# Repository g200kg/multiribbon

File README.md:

# multiribbon

## 開発中

現在開発中の謎楽器です。

複数のリボンコントローラーを並列に並べたフレットレスなギターのような演奏を想定しています。

MCU として XIAO RA4M1 を使用

## Demo

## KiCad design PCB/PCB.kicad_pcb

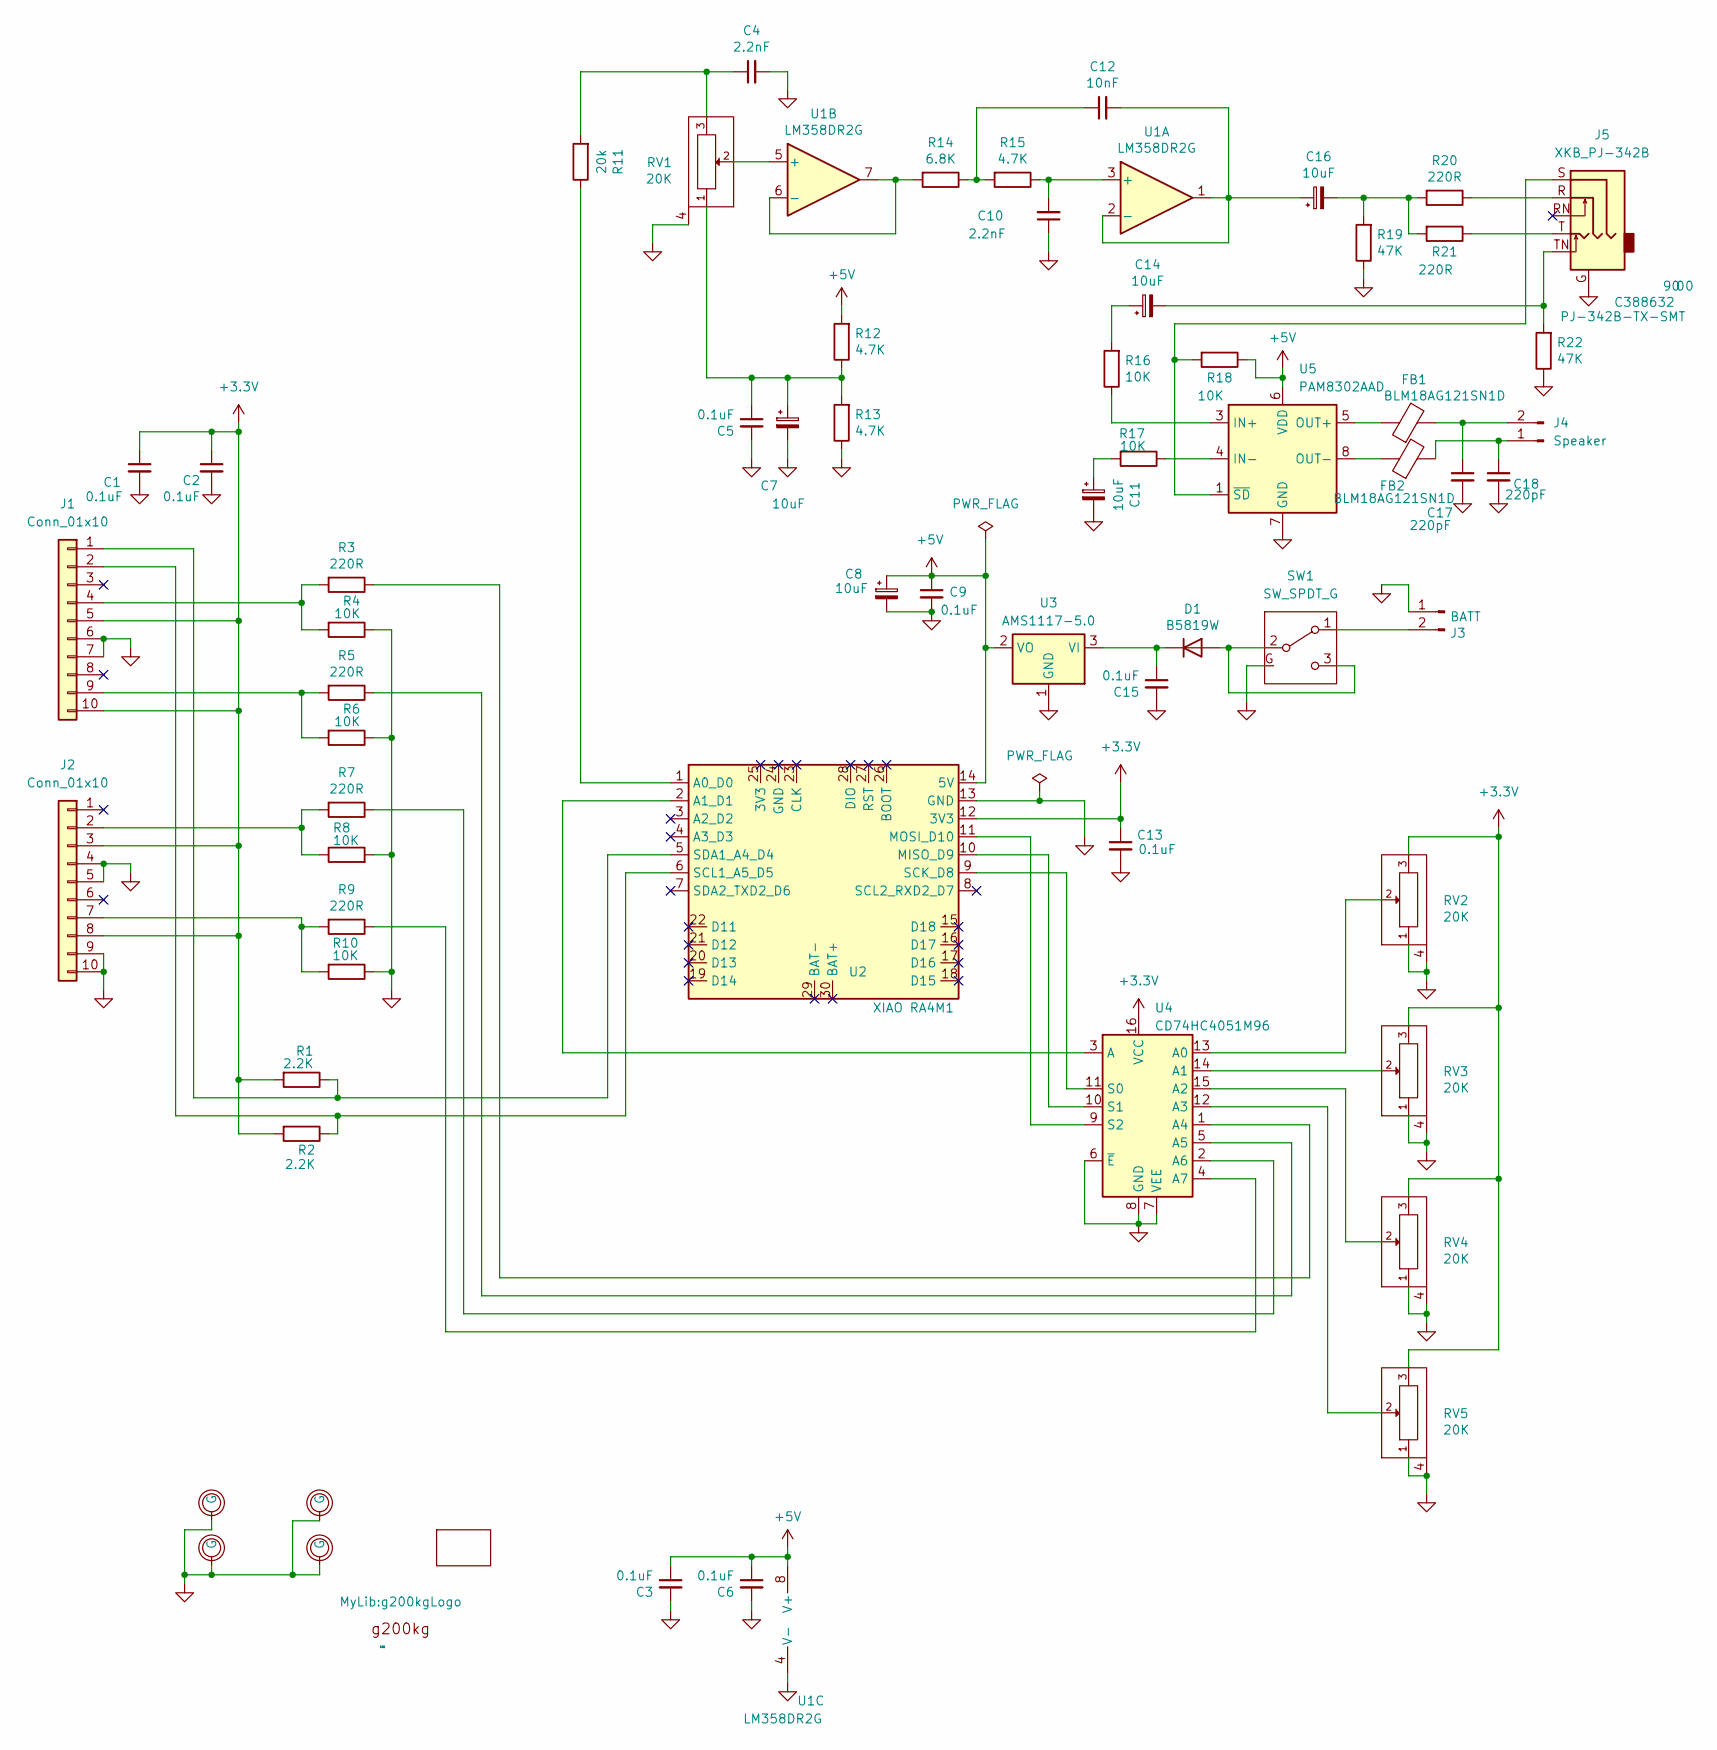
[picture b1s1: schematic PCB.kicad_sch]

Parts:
C1, C2, C3, C5, C6, C9, C13, C15: 0.1uF; C_0603_1608Metric
C4, C10: 2.2nF; C_0603_1608Metric
C7, C8, C11, C14, C16: 10uF; CP_EIA-3216-18_Kemet-A
C12: 10nF; C_0603_1608Metric
C17, C18: 220pF; C_0603_1608Metric
D1: B5819W; D_SOD-123
FB1, FB2: BLM18AG121SN1D; L_0603_1608Metric; LCSC GZ1608D601TF
H1, H2, H3, H4: Hole; MountingHole_3.2mm_M3_DIN965_Pad
J1, J2: Conn_01x10; PinSocket_1x10_P2.54mm_Horizontal
J3: BATT; SolderWire-0.25sqmm_1x02_P4.2mm_D0.65mm_OD1.7mm_Relief
J4: Speaker; JST_PH_S2B-PH-K_1x02_P2.00mm_Horizontal
J5: XKB_PJ-342B; Jack_3.5mm_XKB_PJ342B-TX; LCSC C388632
LG1: LOGO; g200kgLogo
M1: ModuleNC; 006P
R1, R2: 2.2K; R_0603_1608Metric
R3, R5, R7, R9, R20, R21: 220R; R_0603_1608Metric
R4, R6, R8, R10, R16, R17, R18: 10K; R_0603_1608Metric
R11: 20k; R_0603_1608Metric
R12, R13, R15: 4.7K; R_0603_1608Metric
R14: 6.8K; R_0603_1608Metric
R19, R22: 47K; R_0603_1608Metric
RV1, RV2, RV3, RV4, RV5: 20K; Potentiometer_Alps_RK09K_Single_Vertical
SW1: SW_SPDT_G; Sw_Rocker_4MS1R202M6QES
U1: LM358DR2G; SOIC-8_3.9x4.9mm_P1.27mm; LCSC C7950
U2: XIAO RA4M1; XIAO-RA4M1-SMD
U3: AMS1117-5.0; SOT-223-3_TabPin2
U4: CD74HC4051M96; SO-16_3.9x9.9mm_P1.27mm
U5: PAM8302AAD; SOIC-8_3.9x4.9mm_P1.27mm

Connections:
+3.3V: C1.1, C2.1, C13.1, J1.5, J1.10, J2.3, J2.8, R1.2, R2.2, RV2.3, RV3.3, RV4.3, RV5.3, U2.12 (3V3), U4.16 (VCC)
+5V: C3.1, C6.1, C8.1, C9.1, R12.2, R18.1, U1.8 (V+), U2.14 (5V), U3.2 (VO), U5.6 (VDD)
GNDD: C1.2, C2.2, C3.2, C4.2, C5.2, C6.2, C7.2, C8.2, C9.2, C10.1, C11.2, C13.2, C15.2, C17.2, C18.2, H1.1 (G), H2.1 (G), H3.1 (G), H4.1 (G), J1.6, J1.7, J2.4, J2.5, J2.9, J2.10, J3.1, J5.G, R4.1, R6.1, R8.2, R10.1, R13.1, R19.1, R22.1, RV1.4 (G), RV2.1, RV2.4 (G), RV3.1, RV3.4 (G), RV4.1, RV4.4 (G), RV5.1, RV5.4 (G), SW1.G, U1.4 (V-), U2.13 (GND), U3.1 (GND), U4.6 (~E), U4.7 (VEE), U4.8 (GND), U5.7 (GND)
unnamed: C4.1, R11.2, RV1.3
unnamed: C5.1, C7.1, R12.1, R13.2, RV1.1
unnamed: C11.1, R17.2
unnamed: C12.1, R14.1, R15.2
unnamed: C14.1, R16.2
unnamed: C14.2, J5.TN, R22.2
unnamed: C16.2, R19.2, R20.2, R21.2
unnamed: D1.2 (A), SW1.2 (B), SW1.3 (C)
unnamed: C15.1, D1.1 (K), U3.3 (VI)
unnamed: J1.1, R1.1, U2.5 (SDA1_A4_D4)
unnamed: J1.2, R2.1, U2.6 (SCL1_A5_D5)
unnamed: J1.4, R3.2, R4.2
unnamed: J1.9, R5.2, R6.2
unnamed: J2.2, R7.2, R8.1
unnamed: J2.7, R9.2, R10.2
unnamed: J3.2, SW1.1 (A)
unnamed: C18.1, FB2.2, J4.1
unnamed: C17.1, FB1.2, J4.2
unnamed: J5.R, R20.1
unnamed: J5.T, R21.1
unnamed: C10.2, R15.1, U1.3 (+)
unnamed: C12.2, C16.1, U1.1, U1.2 (-)
unnamed: RV1.2, U1.5 (+)
unnamed: R14.2, U1.6 (-), U1.7
unnamed: R11.1, U2.1 (A0_D0)
unnamed: U2.2 (A1_D1), U4.3 (A)
unnamed: U2.10 (MISO_D9), U4.10 (S1)
unnamed: U2.11 (MOSI_D10), U4.9 (S2)
unnamed: U2.9 (SCK_D8), U4.11 (S0)
unnamed: RV2.2, U4.13 (A0)
unnamed: RV3.2, U4.14 (A1)
unnamed: RV4.2, U4.15 (A2)
unnamed: RV5.2, U4.12 (A3)
unnamed: R3.1, U4.1 (A4)
unnamed: R5.1, U4.5 (A5)
unnamed: R7.1, U4.2 (A6)
unnamed: R9.1, U4.4 (A7)
unnamed: R16.1, U5.3 (IN+)
unnamed: R17.1, U5.4 (IN-)
unnamed: FB1.1, U5.5 (OUT+)
unnamed: FB2.1, U5.8 (OUT-)
unnamed: J5.S, R18.2, U5.1 (~SD)

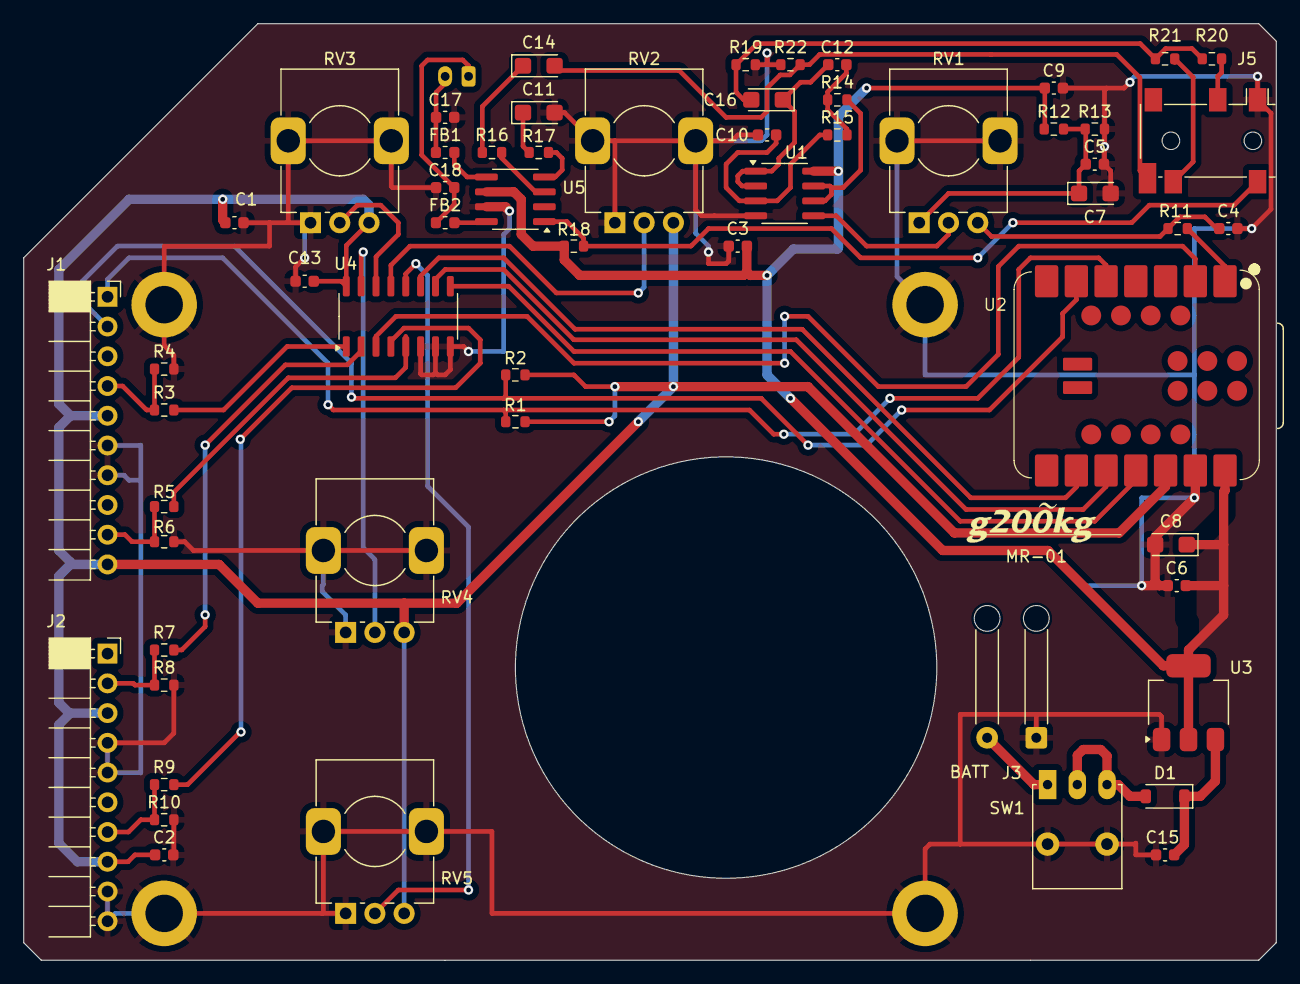
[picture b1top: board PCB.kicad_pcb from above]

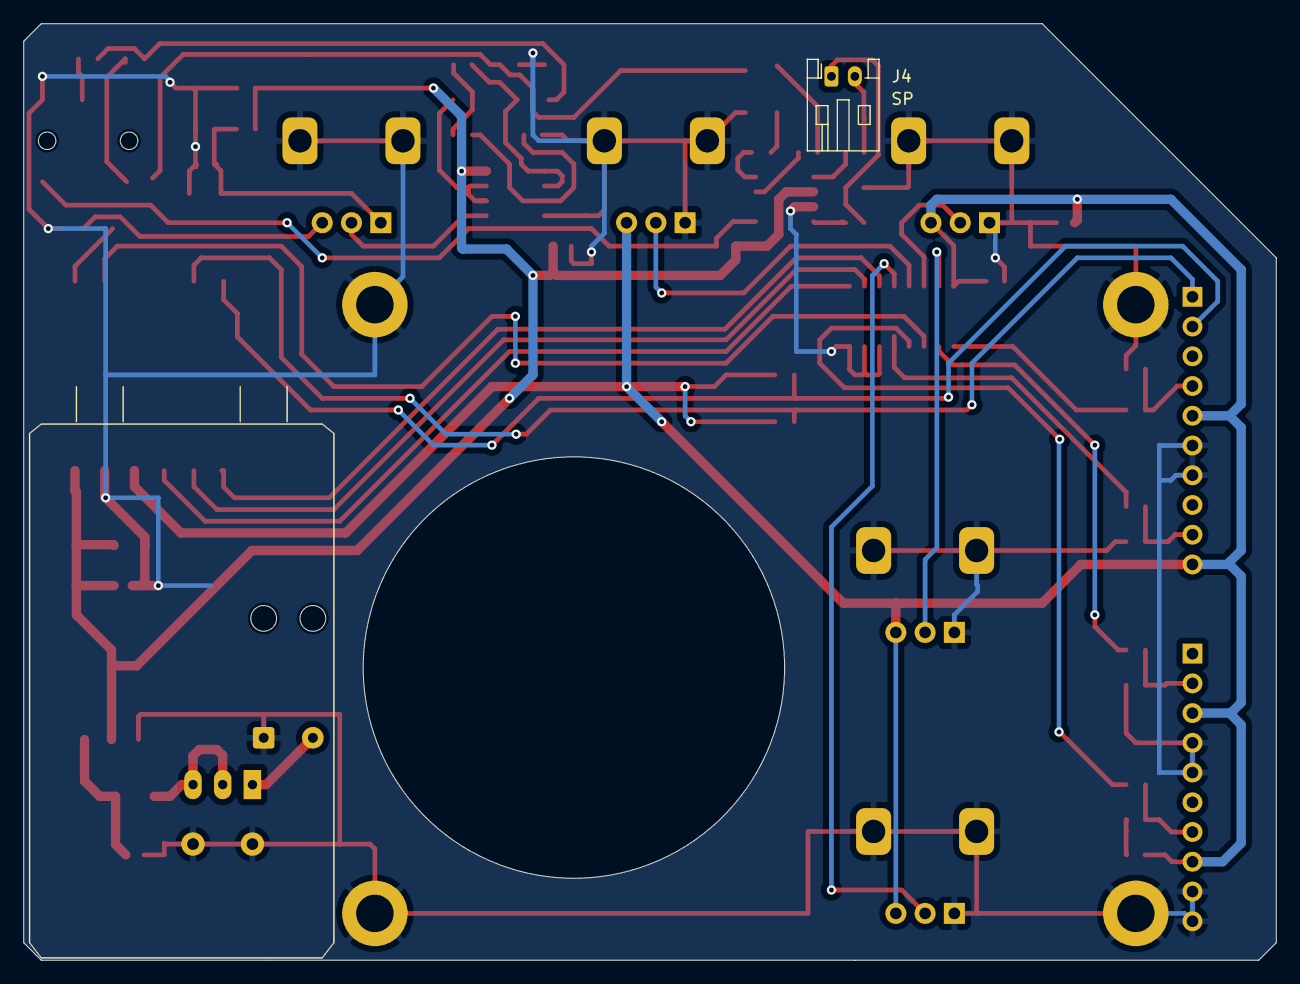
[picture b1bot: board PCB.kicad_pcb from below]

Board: 2 copper layers, 107.0 x 80.0 mm, 65 parts (2 on the bottom side), 45 nets.

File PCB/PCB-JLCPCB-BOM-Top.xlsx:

Comment | Designator | Footprint | JLCPCB Part# | MFR.Part# | Qty
B5819W | D1 | D_SOD-123 | C8598 | B5819W SL | 1
0.1uF | C3,C6,C1,C15,C2,C5,C9,C13 | C_0603_1608Metric | C14663 | CC0603KRX7R9BB104 | 8
10K | R4,R6,R8,R10,R17,R16 | R_0603_1608Metric | C25804 | 0603WAF1002T5E | 6
220R | R3,R5,R7,R9,R20,R21,R18 | R_0603_1608Metric | C22962 | 0603WAF2200T5E | 7
4.7K | R13,R12,R15 | R_0603_1608Metric | C23162 | 0603WAF4701T5E | 3
BLM18AG121SN1D | FB2,FB1 | L_0603_1608Metric | C1002 | GZ1608D601TF | 2
220pF | C18,C17 | C_0603_1608Metric | C1603 | CL10B221KB8NNNC | 2
PAM8302AAD | U5 | SOIC-8_3.9x4.9mm_P1.27mm | C112137 | PAM8302AADCR | 1
10nF | C12 | C_0603_1608Metric | C57112 | 0603B103K500NT | 1
6.8K | R14 | R_0603_1608Metric | C23212 | 0603WAF6801T5E | 1
10uF | C11,C8,C7,C16,C14 | CP_EIA-3216-18_Kemet-A | C7171 | TAJA106K016RNJ | 5
20k | R11 | R_0603_1608Metric | C4184 | 0603WAF2002T5E | 1
2.2K | R2,R1 | R_0603_1608Metric | C4190 | 0603WAF2201T5E | 2
CD74HC4051M96 | U4 | SO-16_3.9x9.9mm_P1.27mm | C132065 | CD74HC4051M96 | 1
XKB_PJ-342B | J5 | Jack_3.5mm_XKB_PJ342B-TX | C388632 | PJ-342B-TX-SMT | 1
LM358DR2G | U1 | SOIC-8_3.9x4.9mm_P1.27mm | C7950 | LM358DR2G | 1
47K | R19,R22 | R_0603_1608Metric | C25819 | 0603WAF4702T5E | 2
2.2nF | C4,C10 | C_0603_1608Metric | C1604 | 0603B222K500NT | 2
AMS1117-5.0 | U3 | SOT-223-3_TabPin2 | C6187 | AMS1117-5.0 | 1

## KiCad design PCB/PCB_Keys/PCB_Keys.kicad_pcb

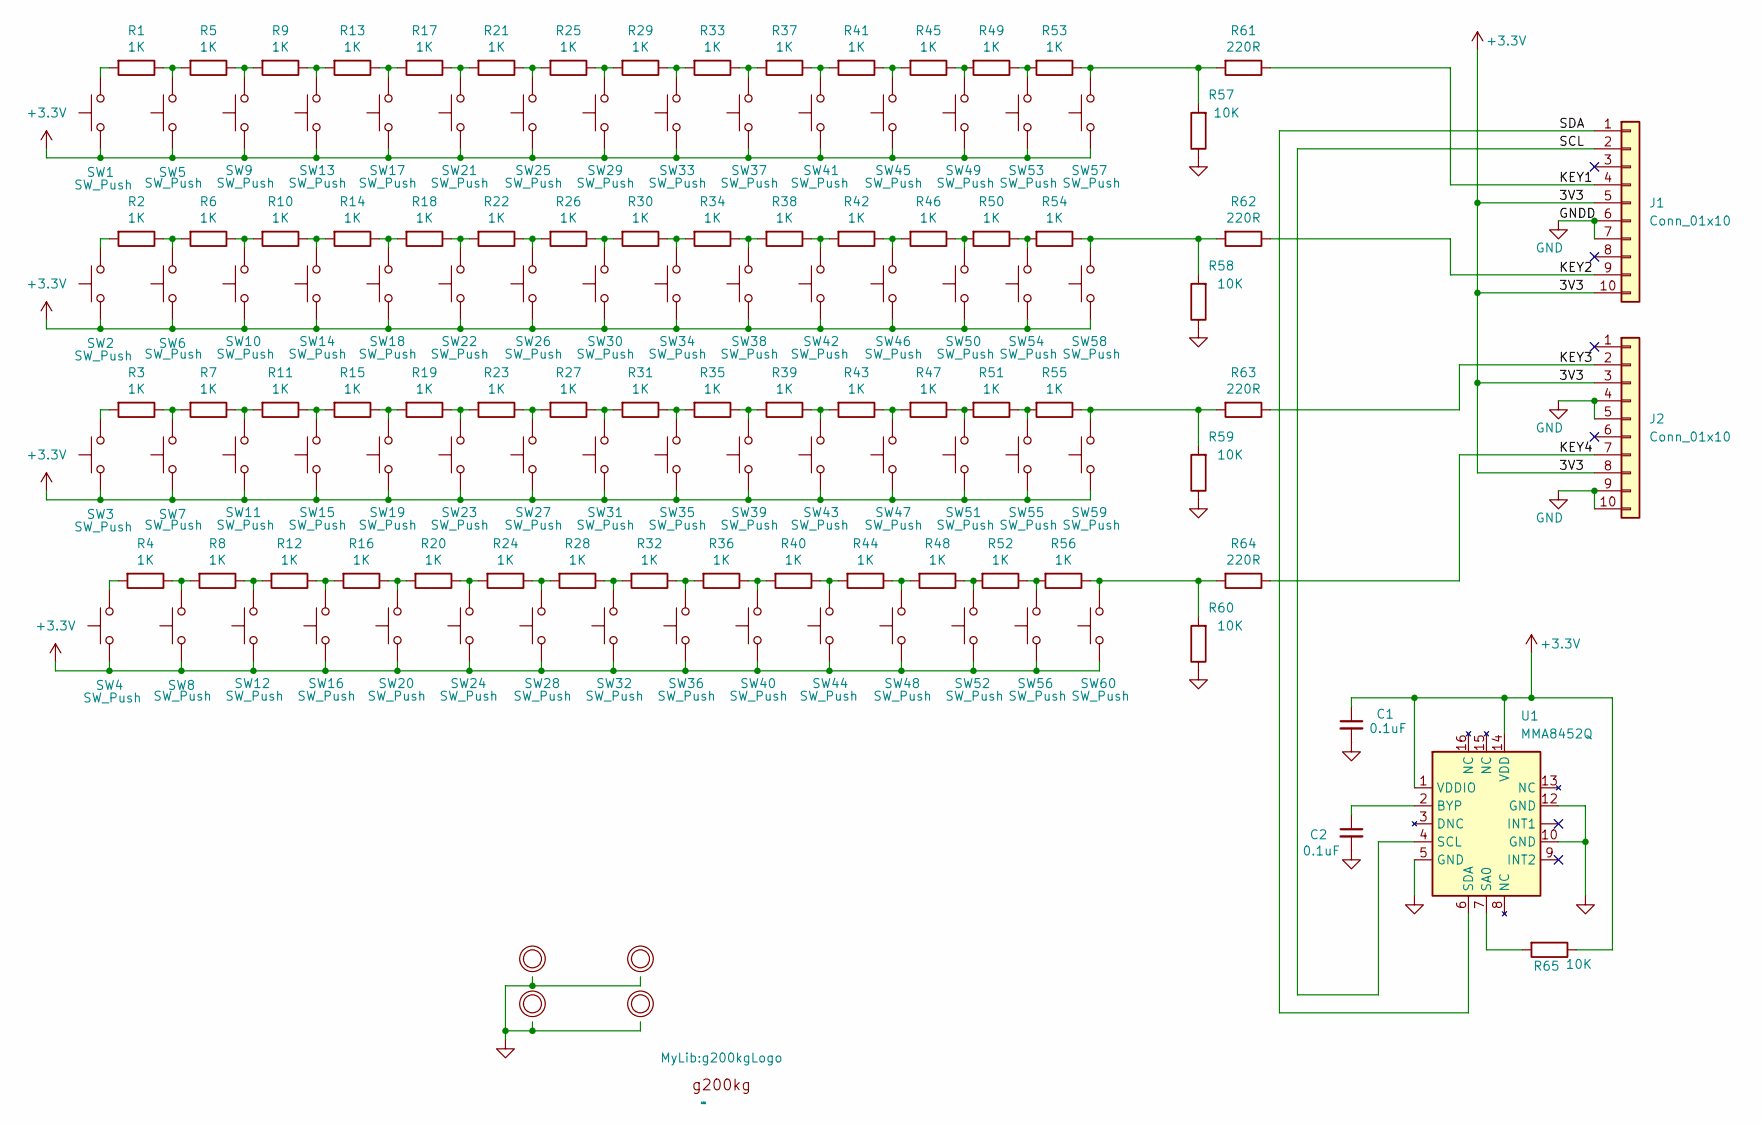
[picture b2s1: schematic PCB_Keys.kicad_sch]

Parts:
C1, C2: 0.1uF; C_0603_1608Metric
H1, H2, H3, H4: Hole; MountingHole_3.2mm_M3_DIN965_Pad
J1, J2: Conn_01x10; PinHeader_1x10_P2.54mm_Horizontal
LG1: LOGO; g200kgLogo
R1, R2, R3, R4, R5, R6, R7, R8, R9, R10, R11, R12, R13, R14, R15, R16, R17, R18, R19, R20, R21, R22, R23, R24, R25, R26, R27, R28, R29, R30, R31, R32, R33, R34, R35, R36, R37, R38, R39, R40, R41, R42, R43, R44, R45, R46, R47, R48, R49, R50, R51, R52, R53, R54, R55, R56: 1K; R_0603_1608Metric
R57, R58, R59, R60, R65: 10K; R_0603_1608Metric
R61, R62, R63, R64: 220R; R_0603_1608Metric
SW1, SW2, SW3, SW4, SW5, SW6, SW7, SW8, SW9, SW10, SW11, SW12, SW13, SW14, SW15, SW16, SW17, SW18, SW19, SW20, SW21, SW22, SW23, SW24, SW25, SW26, SW27, SW28, SW29, SW30, SW31, SW32, SW33, SW34, SW35, SW36, SW37, SW38, SW39, SW40, SW41, SW42, SW43, SW44, SW45, SW46, SW47, SW48, SW49, SW50, SW51, SW52, SW53, SW54, SW55, SW56, SW57, SW58, SW59, SW60: SW_Push; Sw_Push_12x12_SMD
U1: MMA8452Q; QFN16_3x3mm_MMA8452Q

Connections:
+3.3V: C1.1, J1.5, J1.10, J2.3, J2.8, R65.1, SW1.1, SW2.1, SW3.1, SW4.1, SW5.1, SW6.1, SW7.1, SW8.1, SW9.1, SW10.1, SW11.1, SW12.1, SW13.1, SW14.1, SW15.1, SW16.1, SW17.1, SW18.1, SW19.1, SW20.1, SW21.1, SW22.1, SW23.1, SW24.1, SW25.1, SW26.1, SW27.1, SW28.1, SW29.1, SW30.1, SW31.1, SW32.1, SW33.1, SW34.1, SW35.1, SW36.1, SW37.1, SW38.1, SW39.1, SW40.1, SW41.1, SW42.1, SW43.1, SW44.1, SW45.1, SW46.1, SW47.1, SW48.1, SW49.1, SW50.1, SW51.1, SW52.1, SW53.1, SW54.1, SW55.1, SW56.1, SW57.1, SW58.1, SW59.1, SW60.1, U1.1 (VDDIO), U1.14 (VDD)
/KEY1: J1.4, R61.1
/KEY2: J1.9, R62.1
/KEY3: J2.2, R63.1
/KEY4: J2.7, R64.1
/SCL: J1.2, U1.4 (SCL)
/SDA: J1.1, U1.6 (SDA)
GND: C1.2, C2.2, H1.1 (G), H2.1 (G), H3.1 (G), H4.1 (G), J1.6, J1.7, J2.4, J2.5, J2.9, J2.10, R57.1, R58.1, R59.1, R60.1, U1.5 (GND), U1.10 (GND), U1.12 (GND)
unnamed: R1.1, R5.2, SW5.2
unnamed: R1.2, SW1.2
unnamed: R2.1, R6.2, SW6.2
unnamed: R2.2, SW2.2
unnamed: R3.1, R7.2, SW7.2
unnamed: R3.2, SW3.2
unnamed: R4.1, R8.2, SW8.2
unnamed: R4.2, SW4.2
unnamed: R5.1, R9.2, SW9.2
unnamed: R10.1, R14.2, SW14.2
unnamed: R6.1, R10.2, SW10.2
unnamed: R11.1, R15.2, SW15.2
unnamed: R7.1, R11.2, SW11.2
unnamed: R12.1, R16.2, SW16.2
unnamed: R8.1, R12.2, SW12.2
unnamed: R13.1, R17.2, SW17.2
unnamed: R9.1, R13.2, SW13.2
unnamed: R14.1, R18.2, SW18.2
unnamed: R15.1, R19.2, SW19.2
unnamed: R16.1, R20.2, SW20.2
unnamed: R17.1, R21.2, SW21.2
unnamed: R18.1, R22.2, SW22.2
unnamed: R19.1, R23.2, SW23.2
unnamed: R20.1, R24.2, SW24.2
unnamed: R21.1, R25.2, SW25.2
unnamed: R22.1, R26.2, SW26.2
unnamed: R23.1, R27.2, SW27.2
unnamed: R24.1, R28.2, SW28.2
unnamed: R25.1, R29.2, SW29.2
unnamed: R26.1, R30.2, SW30.2
unnamed: R27.1, R31.2, SW31.2
unnamed: R28.1, R32.2, SW32.2
unnamed: R29.1, R33.2, SW33.2
unnamed: R30.1, R34.2, SW34.2
unnamed: R31.1, R35.2, SW35.2
unnamed: R32.1, R36.2, SW36.2
unnamed: R33.1, R37.2, SW37.2
unnamed: R34.1, R38.2, SW38.2
unnamed: R35.1, R39.2, SW39.2
unnamed: R36.1, R40.2, SW40.2
unnamed: R37.1, R41.2, SW41.2
unnamed: R38.1, R42.2, SW42.2
unnamed: R39.1, R43.2, SW43.2
unnamed: R40.1, R44.2, SW44.2
unnamed: R41.1, R45.2, SW45.2
unnamed: R42.1, R46.2, SW46.2
unnamed: R43.1, R47.2, SW47.2
unnamed: R44.1, R48.2, SW48.2
unnamed: R45.1, R49.2, SW49.2
unnamed: R46.1, R50.2, SW50.2
unnamed: R47.1, R51.2, SW51.2
unnamed: R48.1, R52.2, SW52.2
unnamed: R49.1, R53.2, SW53.2
unnamed: R50.1, R54.2, SW54.2
unnamed: R51.1, R55.2, SW55.2
unnamed: R52.1, R56.2, SW56.2
unnamed: R53.1, R57.2, R61.2, SW57.2
unnamed: R54.1, R58.2, R62.2, SW58.2
unnamed: R55.1, R59.2, R63.2, SW59.2
unnamed: R56.1, R60.2, R64.2, SW60.2
unnamed: C2.1, U1.2 (BYP)
unnamed: R65.2, U1.7 (SA0)

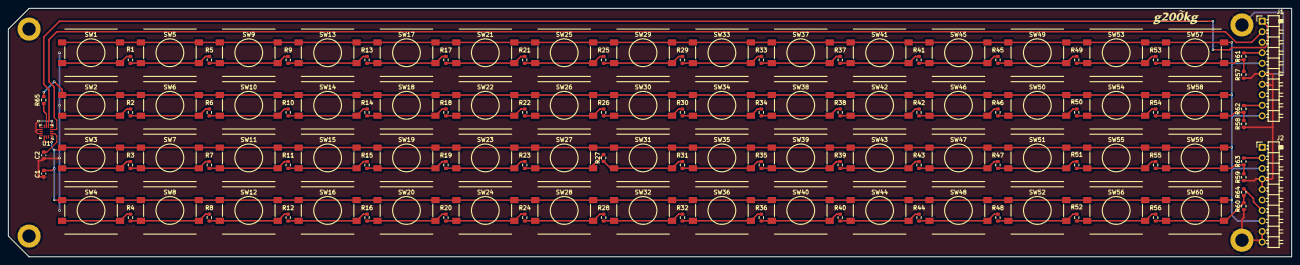
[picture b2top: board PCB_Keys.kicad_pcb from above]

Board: 2 copper layers, 310.0 x 60.0 mm, 135 parts (0 on the bottom side), 70 nets.

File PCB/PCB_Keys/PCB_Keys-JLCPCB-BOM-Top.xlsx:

Comment | Designator | Footprint | JLCPCB Part# | MFR.Part# | Qty
SW_Push | SW30,SW27,SW42,SW4,SW28,SW22,SW3,SW38,SW13,SW55,SW11,SW33,SW26,SW40,SW36,SW21,S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 | Sw_Push_12x12_SMD | C36498966 | HX 12x12x7.3TPFT-B | 60
1K | R11,R49,R20,R19,R56,R9,R40,R51,R1,R7,R29,R23,R42,R41,R33,R44,R46,R24,R55,R37,R4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 | R_0603_1608Metric | C21190 | 0603WAF1001T5E | 56
10K | R58,R60,R59,R57,R65 | R_0603_1608Metric | C25804 | 0603WAF1002T5E | 5
220R | R64,R63,R61,R62 | R_0603_1608Metric | C22962 | 0603WAF2200T5E | 4
0.1uF | C2,C1 | C_0603_1608Metric | C14663 | CC0603KRX7R9BB104 | 2
MMA8452Q | U1 | QFN16_3x3mm_MMA8452Q | C11360 | MMA8452QR1 | 1

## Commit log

2025-05-15 add blender files
2025-05-18 add pcb data
2025-05-18 Revert "add pcb data"
    This reverts commit 672ffdb4691e8e0b232305007696bea88e0432db.
2025-05-23 add files
2025-05-23 fix link
2025-05-23 add arduino files
